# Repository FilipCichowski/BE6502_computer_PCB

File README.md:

<div id="header" align="center">
  
  <div id="badges">

  </div>
</div>

# BE6502 :keyboard:
[Ben Eater](https://eater.net/) has been a huge inspiration for many getting into building computers using basic electronic building blocks, his [videos](https://www.youtube.com/user/eaterbc) are truly excellent and it is no wonder he's often referred to as the Bob Ross of Breadboards! His latest project is [building a 6502 computer](https://eater.net/6502) on a breadboard, a video series that I'm sure will also inspire a lot of new users to the art of building stuff with the 6502! Check out the main [README](https://github.com/tebl/BE6502) for an overview of all the modules available to the BE6502 computer.

## Computer (SBC-module) :computer:
This module specifically contains all of the modules that makes the BE6502 an actual computer, it has the CPU, RAM, ROM and a way of interacting with the world using the VIA-chip. Also described as an SBC-module which means that it is a *Single Board Computer* though I'm certainly a fan of building more things around it, I just look at it has giving the computer more tricks that it can use to both entertain and educate us at the same time.

As you can see, I've also got the 1 Mhz oscillator installed as it is listed in Ben Eaters design though it is not connected by default so that the adjustable or manual clock can be used instead - to enable the 1 Mhz clock you'll need to install a jumper as shown below.

I did however have some issues running the CPU reliably at this speed, this is due to the reset circuit specified not being suitable for use at anything other than very low speeds. While we're probably waiting for part 8 of the video series to fix this issue, you can build one yourself on a breadboard with just about the same parts seen earlier in the series.

The hardware solution I'm using is a somewhat simplified version of the one at [RC6502 Reset Circuit](https://github.com/tebl/RC6502-Apple-1-Replica/tree/master/RC6502%20Reset%20Circuit), this is mainly by leaving out the oscillator (since we've already got one) and the 74LS74. For masters of the Commodore 64 the circuit will seem familiar, this is because it's the one originally used on its boards! Alternatively as a software solution, the Arduino Mega can also be used to perform this task - this is done by holding down the first switch (since revision B of the Mega Adapter) or by typing in reset via the serial interface.

## Jumpers
| Reference | Position | Description                                        |
| --------- | -------- | -------------------------------------------------- |
| LCD_EN    | 1-2      | Enable LCD                                         |
|           | 2-3 *    | Disable LCD without physically removing it         |
| LED_EN    | o-o *    | Jumpered to enable port B LEDs                     |
| CLOCK_SEL | 1   **   | VCC                                                |
|           | 2-3 **   | Jumper to enable 1 Mhz clock                       |
|           | 4   **   | GND                                                |

*) Marks the default jumpered positions when performing tasks associated with the first parts of the video series. Later, when the LCD is introduced, these will have to be changed.

**) CLOCK_SEL is also used as a connector when connecting the clock module, the pins are made to directly match the 4 positions on both modules. Pins 2-3 should only be jumpered when using 1Mhz clock, but you can also use pins 1 and 4 when powering other circuits. 

# Schematic :blue_book:
The supplied KiCad files should be sufficient as both a schematic and as a starting point for ordering PCBs (basically you could just zip the contents of the export folder and upload that on a fabrication site), the schematic is also available in [PDF-format](https://github.com/tebl/BE6502/raw/master/BE6502%20SBC/export/BE6502%20SBC.pdf) so that you can refer to it while troubleshooting. You could even print it out and hang it on your office wall, excellent conversation starter at any technology-oriented business worth working at (or so I keep telling myself)!

*) R18 was added to SBC revision B boards as I had forgotten to add the pull-up for the BE-line, causing instability on the boards due to it floating around. Refer to this [picture](https://github.com/tebl/BE6502-Build-a-65c02-computer/raw/master/gallery/2020-02-16%2015.50.14-1.jpg) for a convenient spot to add it to revision A boards.

When constructing the board I recommend using 60/40 solder as the lead-free is more trouble than it's worth for hobby use, take your time with it and try to build up the board starting with the lowest components before moving on to the larger pieces. The LCD will be mounted on top of other components, so check that nothing shorts on the underside and unless you're 100% sure about the construction and my design - install some female header pins on it so that you can easily remove it while troubleshooting the circuit underneath!

# PCB :package:
I created PCB using Topor Lite autorouter. "autoroute" folder contain necessary files. 

# Authors :hammer:
I've just created different, better in my opinion PCB. Original KiCad files belongs to tebl. Link to his profile: https://github.com/tebl

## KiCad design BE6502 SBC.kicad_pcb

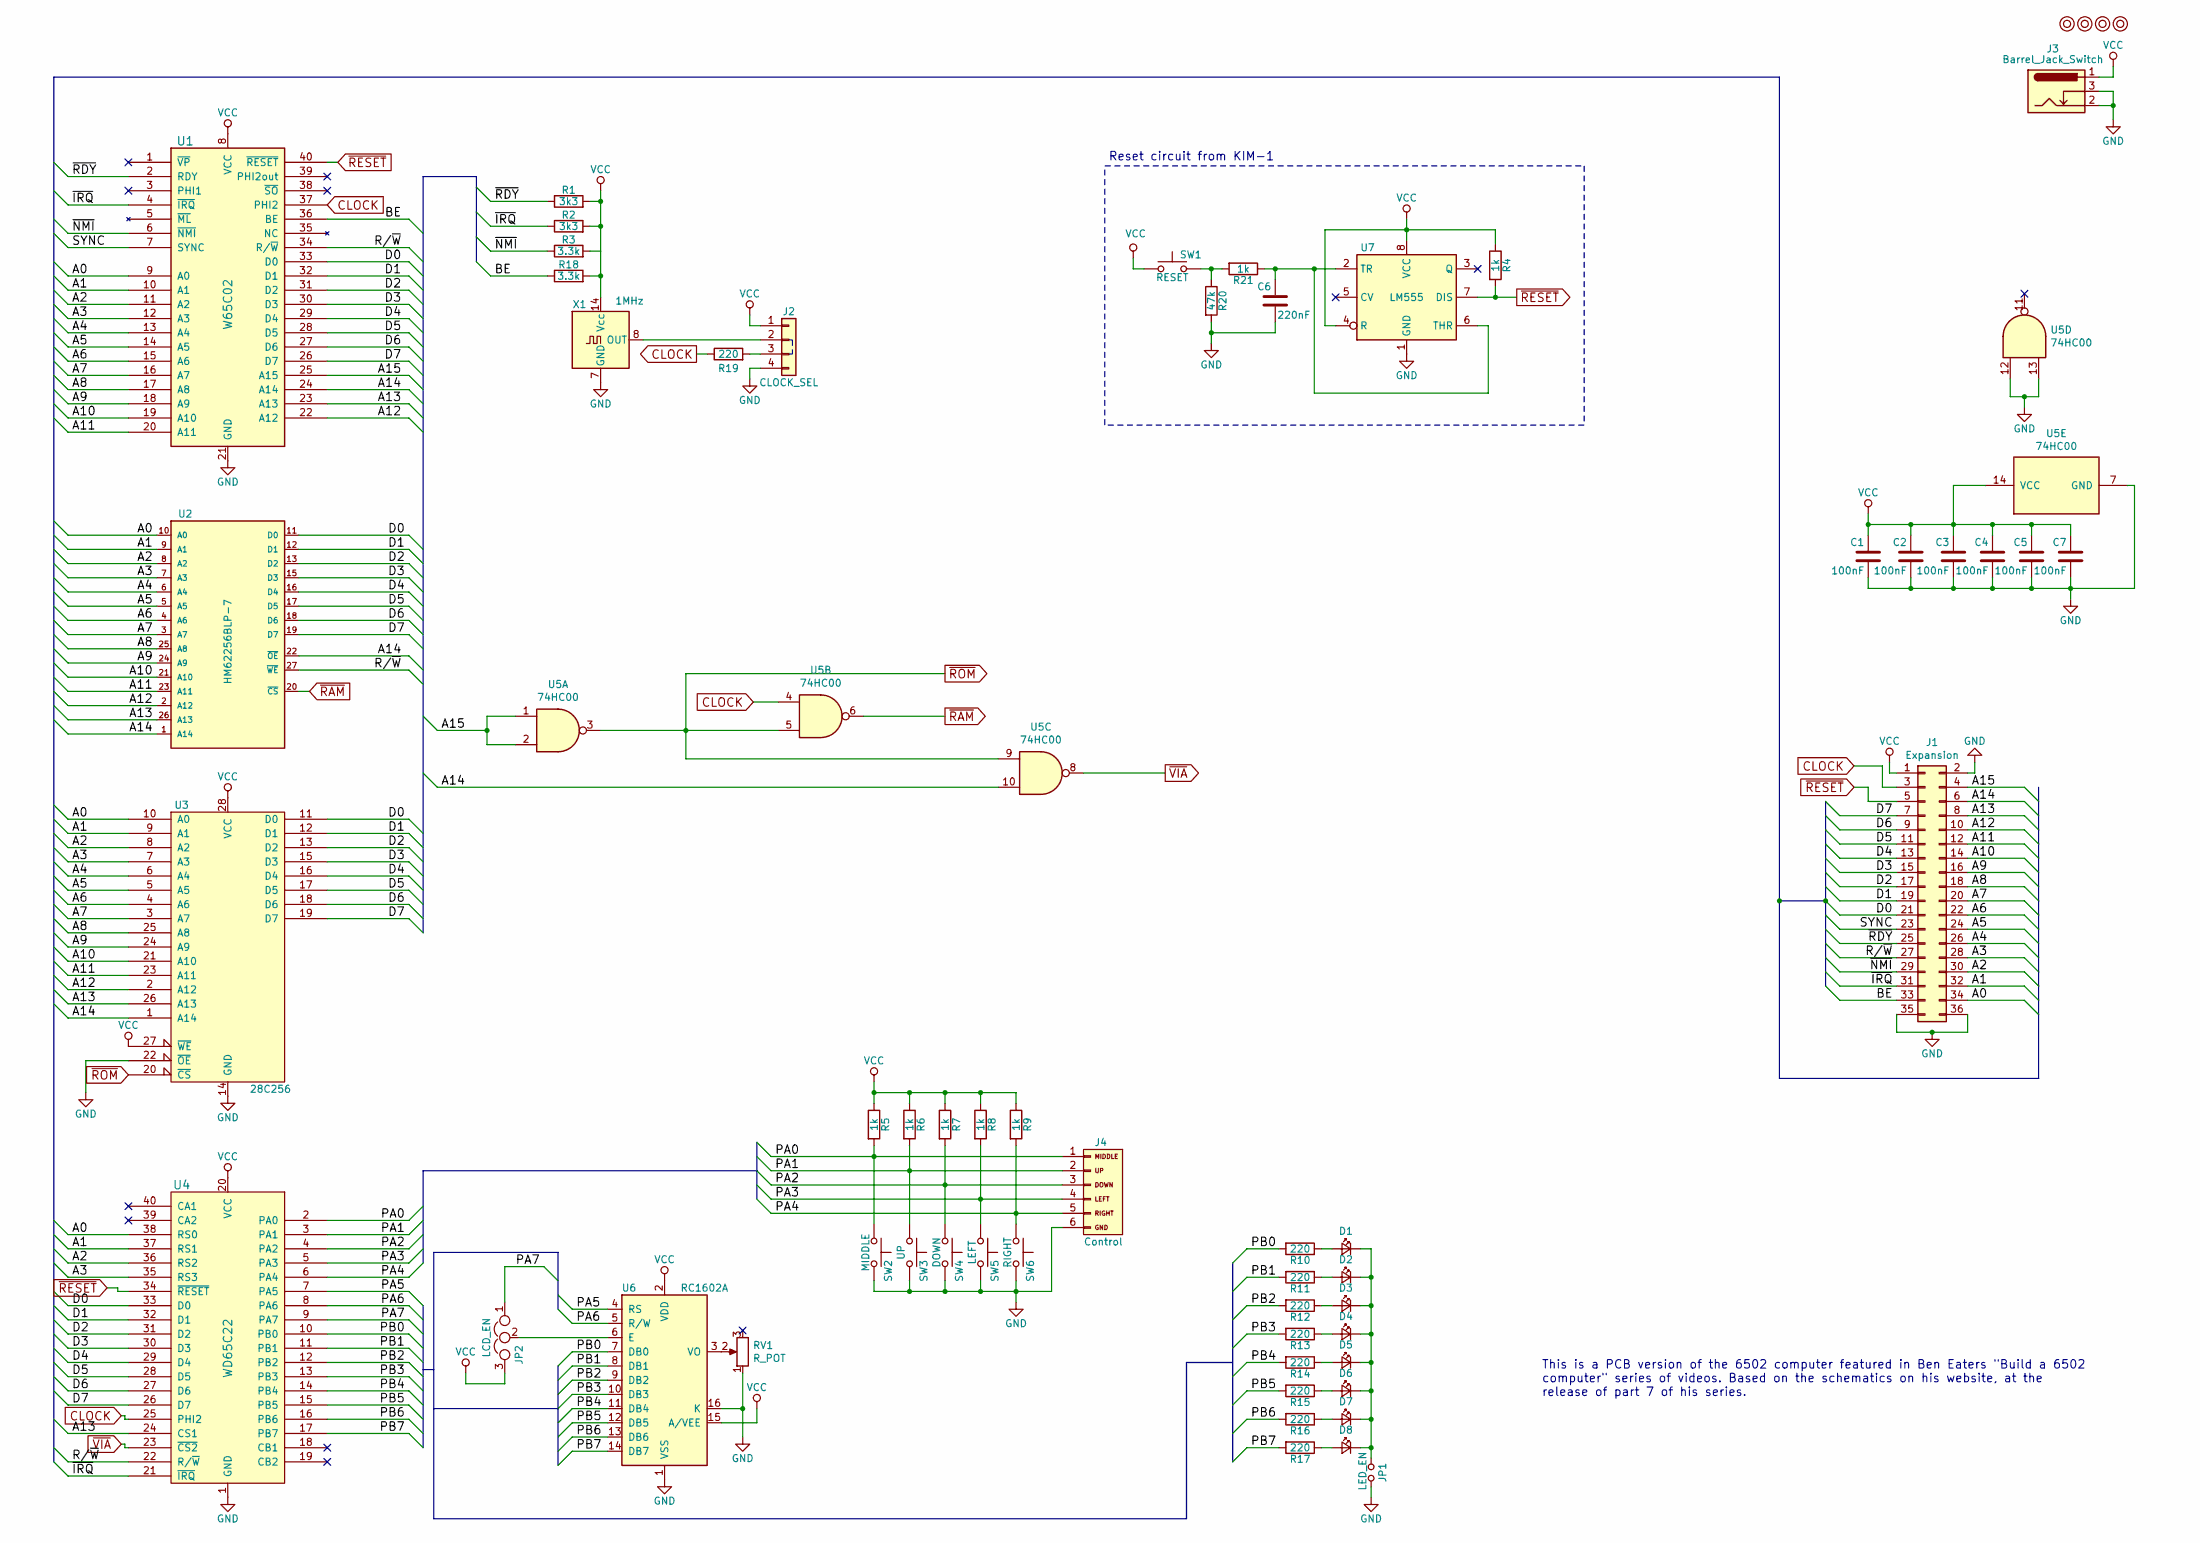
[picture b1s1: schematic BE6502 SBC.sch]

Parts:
C1, C2, C3, C4, C5, C7: 100nF; C_1206_3216Metric_Pad1.42x1.75mm_HandSolder
C6: 220nF; C_1206_3216Metric_Pad1.42x1.75mm_HandSolder
D1, D2, D3, D4, D5, D6, D7, D8: LED; LED_D5.0mm
J1: Expansion; PinSocket_2x18_P2.54mm_Vertical
J2: CLOCK_SEL; PinSocket_1x04_P2.54mm_Vertical
J3: Barrel_Jack_Switch; BarrelJack_Horizontal
J4: Control; PinSocket_1x06_P2.54mm_Vertical
JP1: LED_EN; PinSocket_1x02_P2.54mm_Vertical
JP2: LCD_EN; PinSocket_1x03_P2.54mm_Vertical
M1, M2, M3, M4: Mounting; 1pin
R1, R2: 3k3; R_1206_3216Metric_Pad1.42x1.75mm_HandSolder
R3, R18: 3.3k; R_1206_3216Metric_Pad1.42x1.75mm_HandSolder
R4, R5, R6, R7, R8, R9, R21: 1k; R_1206_3216Metric_Pad1.42x1.75mm_HandSolder
R10, R11, R12, R13, R14, R15, R16, R17, R19: 220; R_1206_3216Metric_Pad1.42x1.75mm_HandSolder
R20: 47k; R_1206_3216Metric_Pad1.42x1.75mm_HandSolder
RV1: R_POT; Potentiometer_Bourns_3296W_Vertical
SW1: RESET; SW_PUSH_6mm
SW2: MIDDLE; SW_PUSH_6mm
SW3: UP; SW_PUSH_6mm
SW4: DOWN; SW_PUSH_6mm
SW5: LEFT; SW_PUSH_6mm
SW6: RIGHT; SW_PUSH_6mm
U1: W65C02; DIP-40_W15.24mm_Socket_LongPads
U2: HM62256BLP-7; DIP-28_W15.24mm_Socket_LongPads
U3: 28C256; DIP-28_W15.24mm_Socket_LongPads
U4: WD65C22; DIP-40_W15.24mm_Socket_LongPads
U5: 74HC00; DIP-14_W7.62mm_LongPads
U6: RC1602A; WC1602A
U7: LM555; DIP-8_W7.62mm_Socket_LongPads
X1: 1MHz; Oscillator_DIP-14

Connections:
/A0: J1.34, U1.9 (A0), U2.10 (A0), U3.10 (A0), U4.38 (RS0)
/A1: J1.32, U1.10 (A1), U2.9 (A1), U3.9 (A1), U4.37 (RS1)
/A2: J1.30, U1.11 (A2), U2.8 (A2), U3.8 (A2), U4.36 (RS2)
/A3: J1.28, U1.12 (A3), U2.7 (A3), U3.7 (A3), U4.35 (RS3)
/A4: J1.26, U1.13 (A4), U2.6 (A4), U3.6 (A4)
/A5: J1.24, U1.14 (A5), U2.5 (A5), U3.5 (A5)
/A6: J1.22, U1.15 (A6), U2.4 (A6), U3.4 (A6)
/A7: J1.20, U1.16 (A7), U2.3 (A7), U3.3 (A7)
/A8: J1.18, U1.17 (A8), U2.25 (A8), U3.25 (A8)
/A9: J1.16, U1.18 (A9), U2.24 (A9), U3.24 (A9)
/A10: J1.14, U1.19 (A10), U2.21 (A10), U3.21 (A10)
/A11: J1.12, U1.20 (A11), U2.23 (A11), U3.23 (A11)
/A12: J1.10, U1.22 (A12), U2.2 (A12), U3.2 (A12)
/A13: J1.8, U1.23 (A13), U2.26 (A13), U3.26 (A13), U4.24 (CS1)
/A14: J1.6, U1.24 (A14), U2.1 (A14), U2.22 (~OE), U3.1 (A14), U5.10
/A15: J1.4, U1.25 (A15), U5.1, U5.2
/BE: J1.33, R18.1, U1.36 (BE)
/D0: J1.21, U1.33 (D0), U2.11 (D0), U3.11 (D0), U4.33 (D0)
/D1: J1.19, U1.32 (D1), U2.12 (D1), U3.12 (D1), U4.32 (D1)
/D2: J1.17, U1.31 (D2), U2.13 (D2), U3.13 (D2), U4.31 (D2)
/D3: J1.15, U1.30 (D3), U2.15 (D3), U3.15 (D3), U4.30 (D3)
/D4: J1.13, U1.29 (D4), U2.16 (D4), U3.16 (D4), U4.29 (D4)
/D5: J1.11, U1.28 (D5), U2.17 (D5), U3.17 (D5), U4.28 (D5)
/D6: J1.9, U1.27 (D6), U2.18 (D6), U3.18 (D6), U4.27 (D6)
/D7: J1.7, U1.26 (D7), U2.19 (D7), U3.19 (D7), U4.26 (D7)
/PA0: J4.1 (MIDDLE), R5.2, SW2.1, U4.2 (PA0)
/PA1: J4.2 (UP), R6.2, SW3.1, U4.3 (PA1)
/PA2: J4.3 (DOWN), R7.2, SW4.1, U4.4 (PA2)
/PA3: J4.4 (LEFT), R8.2, SW5.1, U4.5 (PA3)
/PA4: J4.5 (RIGHT), R9.2, SW6.1, U4.6 (PA4)
/PA5: U4.7 (PA5), U6.4 (RS)
/PA6: U4.8 (PA6), U6.5 (R/W)
/PA7: JP2.1, U4.9 (PA7)
/PB0: R10.2, U4.10 (PB0), U6.7 (DB0)
/PB1: R11.2, U4.11 (PB1), U6.8 (DB1)
/PB2: R12.2, U4.12 (PB2), U6.9 (DB2)
/PB3: R13.2, U4.13 (PB3), U6.10 (DB3)
/PB4: R14.2, U4.14 (PB4), U6.11 (DB4)
/PB5: R15.2, U4.15 (PB5), U6.12 (DB5)
/PB6: R16.2, U4.16 (PB6), U6.13 (DB6)
/PB7: R17.2, U4.17 (PB7), U6.14 (DB7)
/R/~W: J1.27, U1.34 (R/~W), U2.27 (~WE), U4.22 (R/~W)
/SYNC: J1.23, U1.7 (SYNC)
/~IRQ: J1.31, R2.1, U1.4 (~IRQ), U4.21 (~IRQ)
/~NMI: J1.29, R3.1, U1.6 (~NMI)
/~RDY: J1.25, R1.1, U1.2 (RDY)
CLOCK: J1.3, R19.1, U1.37 (PHI2), U4.25 (PHI2), U5.4
GND: C1.2, C2.2, C3.2, C4.2, C5.2, C6.2, C7.2, J1.2, J1.35, J1.36, J2.4, J3.2, J3.3, J4.6 (GND), JP1.1, R20.2, RV1.1, SW2.2, SW3.2, SW4.2, SW5.2, SW6.2, U1.21 (GND), U2.14 (GND), U3.14 (GND), U3.22 (~OE), U4.1 (GND), U5.7 (GND), U5.12, U5.13, U6.1 (VSS), U6.16 (K), U7.1 (GND), X1.7 (GND)
unnamed: C6.1, R21.1, U7.2 (TR), U7.6 (THR)
unnamed: D1.1 (K), D2.1 (K), D3.1 (K), D4.1 (K), D5.1 (K), D6.1 (K), D7.1 (K), D8.1 (K), JP1.2
unnamed: D1.2 (A), R10.1
unnamed: D2.2 (A), R11.1
unnamed: D3.2 (A), R12.1
unnamed: D4.2 (A), R13.1
unnamed: D5.2 (A), R14.1
unnamed: D6.2 (A), R15.1
unnamed: D7.2 (A), R16.1
unnamed: D8.2 (A), R17.1
unnamed: J2.2, X1.8 (OUT)
unnamed: J2.3, R19.2
unnamed: JP2.2, U6.6 (E)
unnamed: R20.1, R21.2, SW1.2
unnamed: RV1.2, U6.3 (VO)
VCC: C1.1, C2.1, C3.1, C4.1, C5.1, C7.1, J1.1, J2.1, J3.1, JP2.3, R1.2, R2.2, R3.2, R4.1, R5.1, R6.1, R7.1, R8.1, R9.1, R18.2, SW1.1, U1.8 (VCC), U2.28 (VCC), U3.27 (~WE), U3.28 (VCC), U4.20 (VCC), U5.14 (VCC), U6.2 (VDD), U6.15 (A/VEE), U7.4 (R), U7.8 (VCC), X1.14 (Vcc)
~RAM: U2.20 (~CS), U5.6
~RESET: J1.5, R4.2, U1.40 (~RESET), U4.34 (~RESET), U7.7 (DIS)
~ROM: U3.20 (~CS), U5.3, U5.5, U5.9
~VIA: U4.23 (~CS2), U5.8

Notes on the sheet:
This is a PCB version of the 6502 computer featured in Ben Eaters "Build a 6502 computer" series of videos. Based on the schematics on his website, at the release of part 7 of his series.
Reset circuit from KIM-1

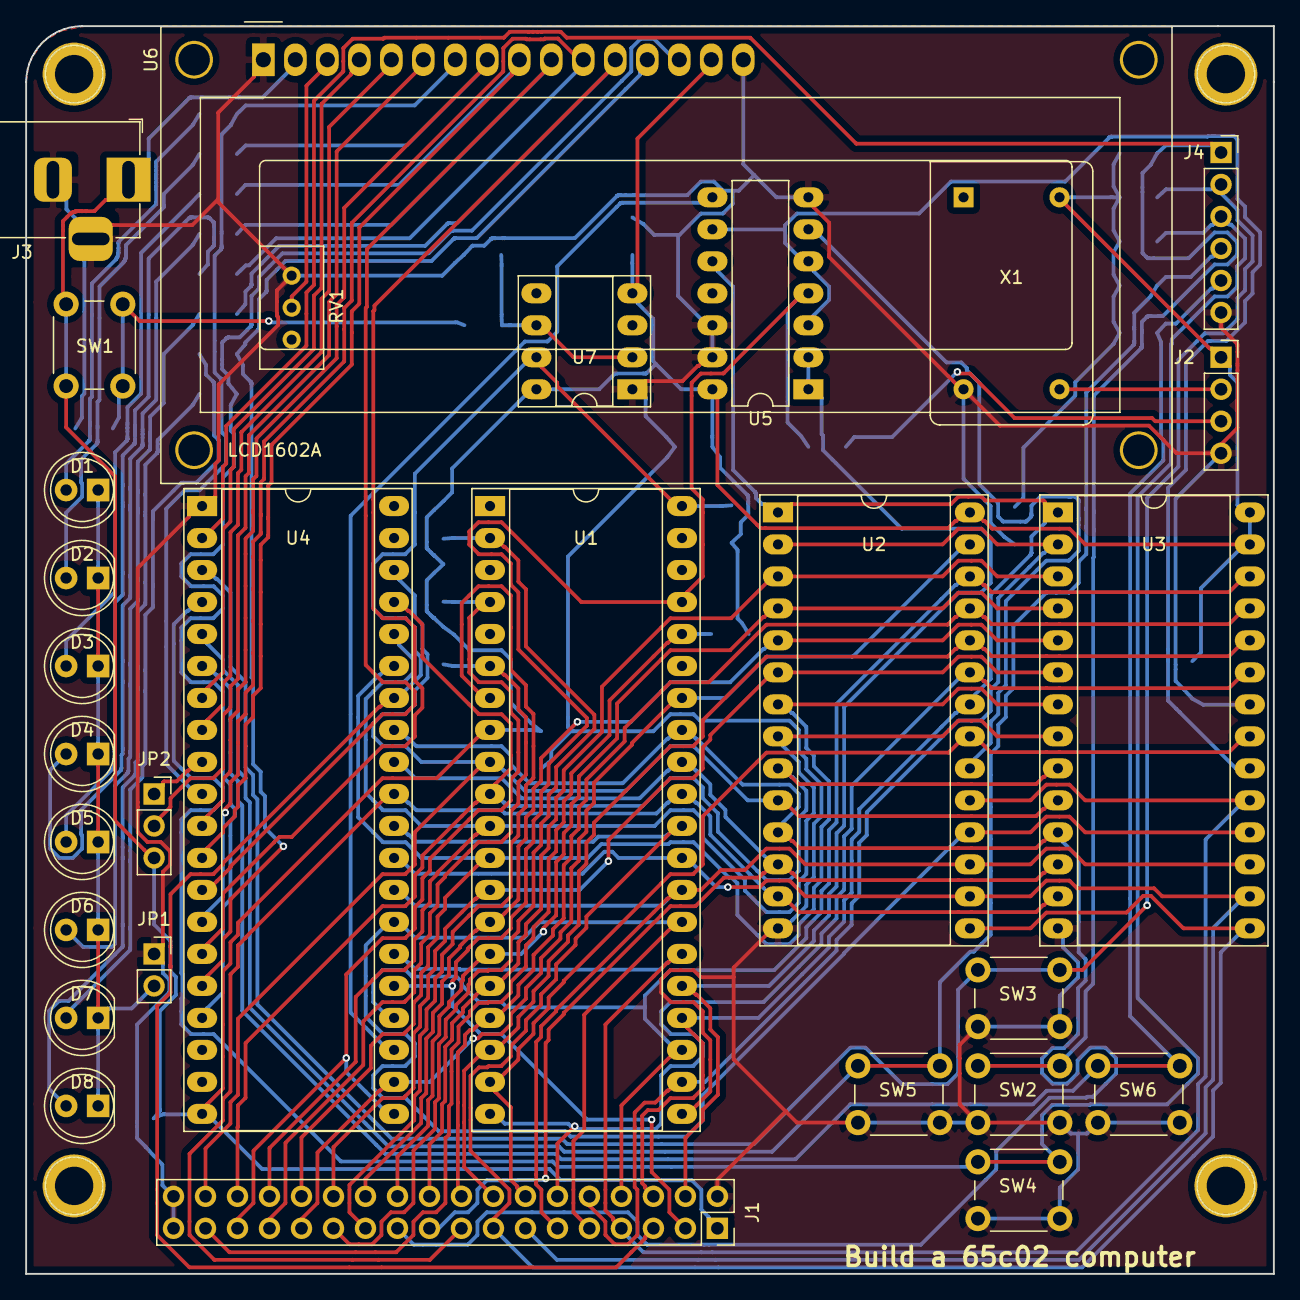
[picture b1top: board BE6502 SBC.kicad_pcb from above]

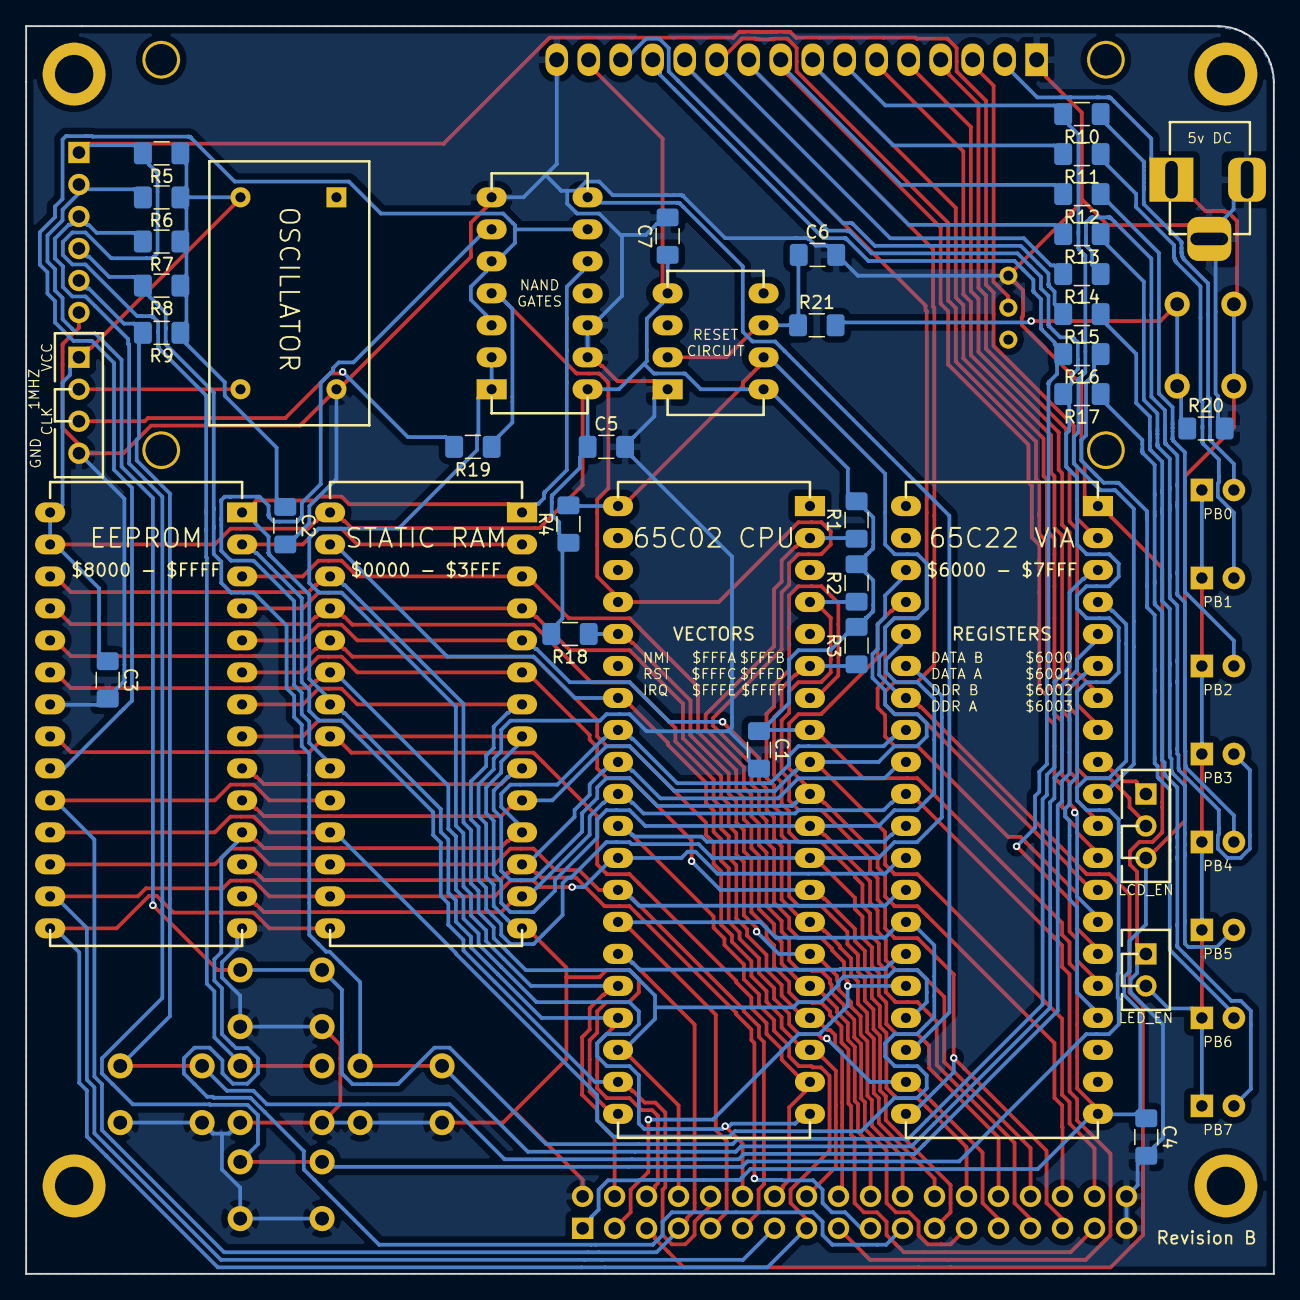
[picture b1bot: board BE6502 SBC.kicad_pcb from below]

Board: 2 copper layers, 99.1 x 99.1 mm, 61 parts (28 on the bottom side), 68 nets.
